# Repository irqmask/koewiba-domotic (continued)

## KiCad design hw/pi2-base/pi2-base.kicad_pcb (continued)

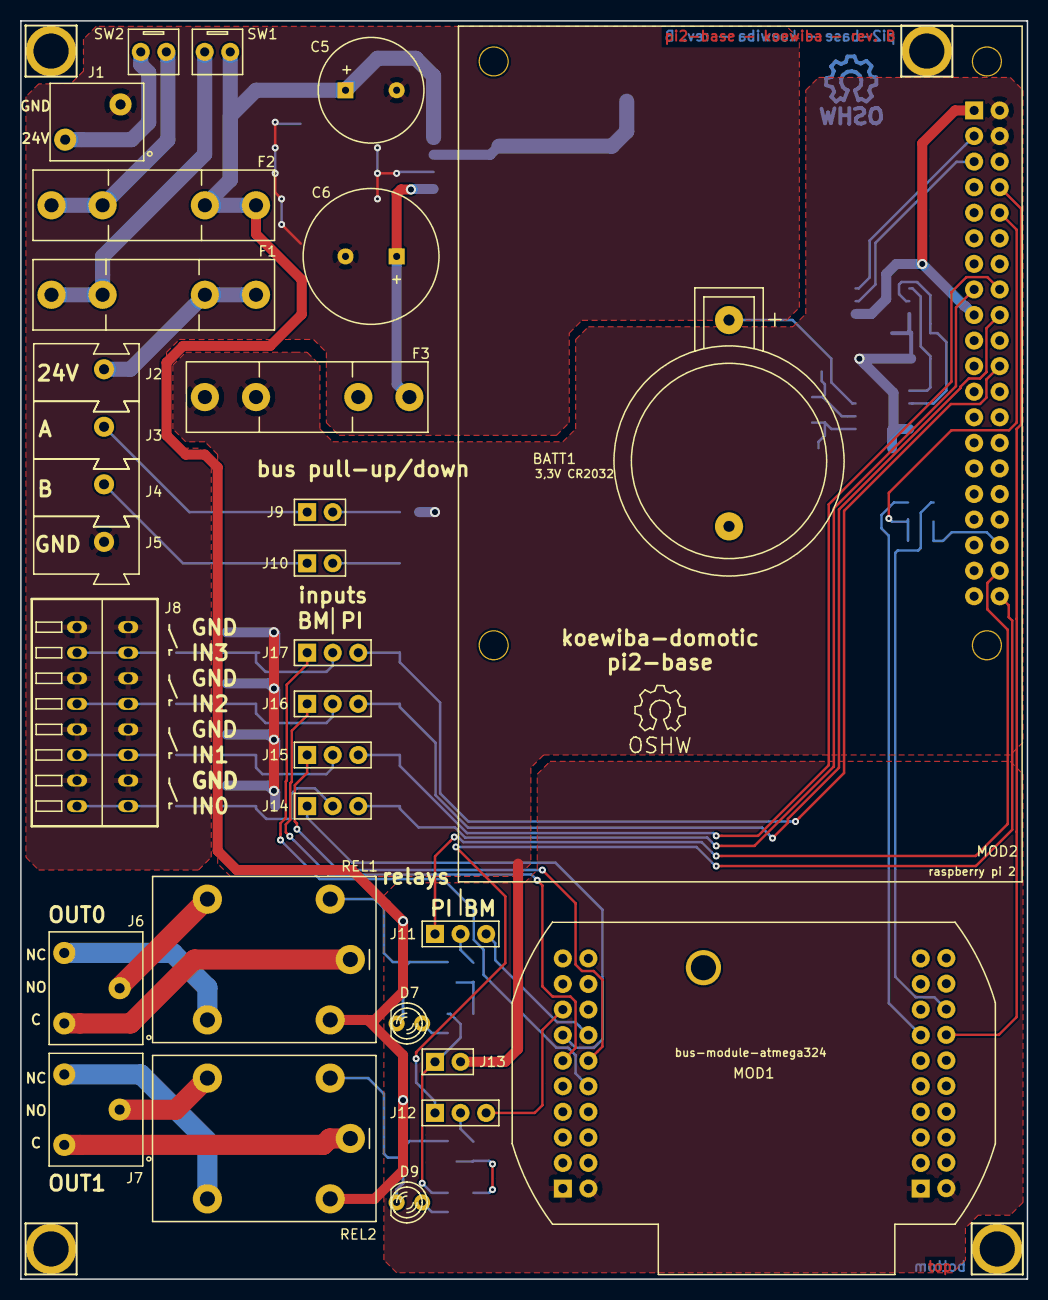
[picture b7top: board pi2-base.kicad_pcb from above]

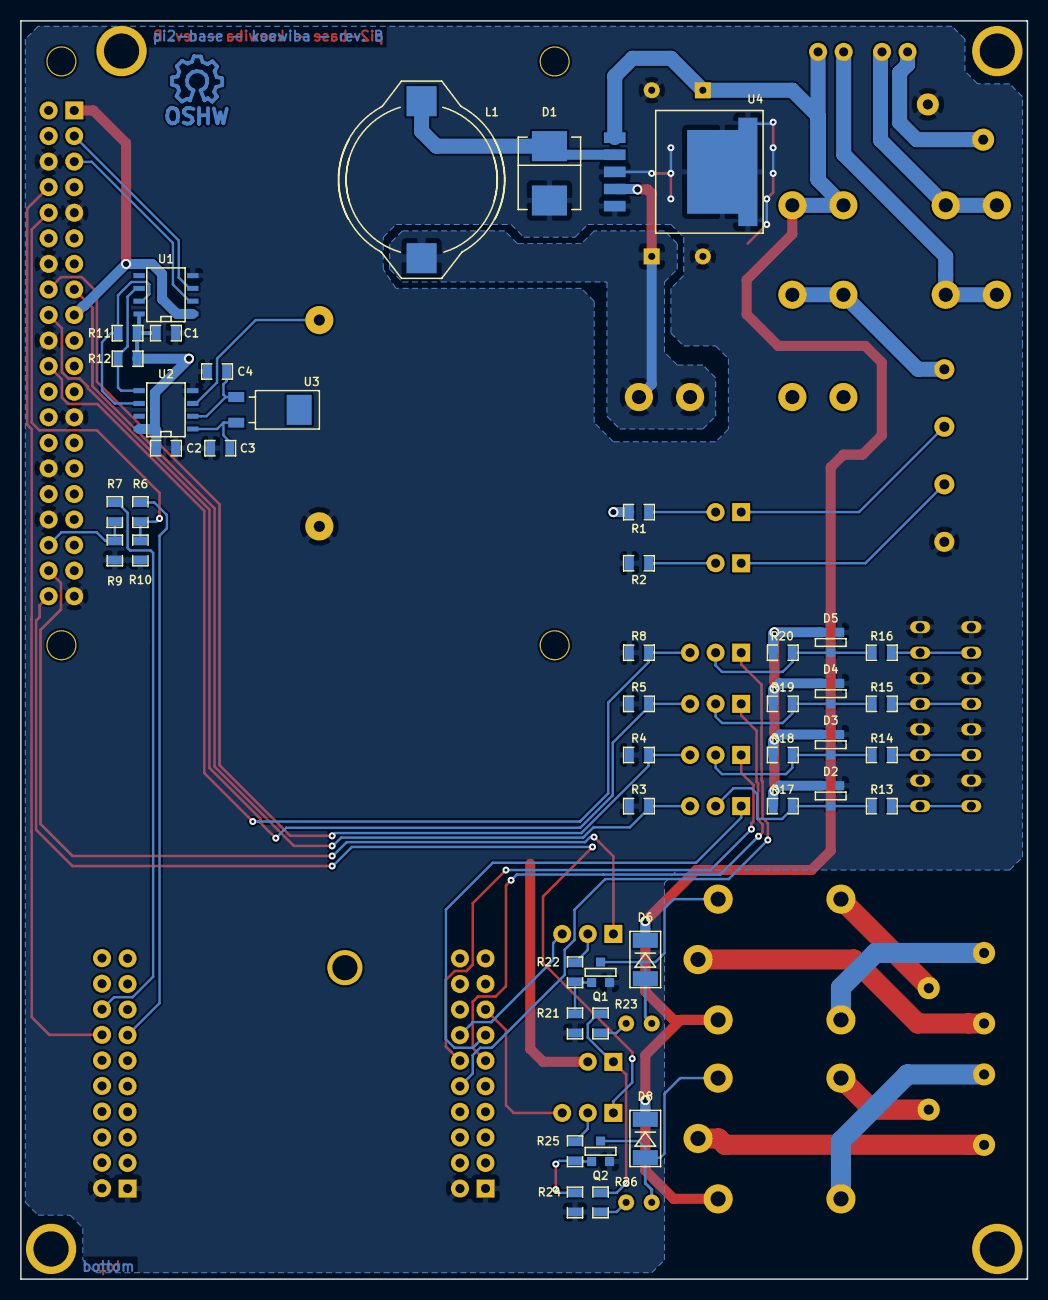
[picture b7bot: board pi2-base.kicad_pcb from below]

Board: 2 copper layers, 100.0 x 125.0 mm, 81 parts (45 on the bottom side), 61 nets.

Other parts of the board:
Symbol_OSHW-Logo_SilkScreen: Open Source Hardware; Symbol_OSHW-Logo_SilkScreen

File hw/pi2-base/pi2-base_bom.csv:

"Id";"Bezeichner";"Gehäuse";"Stückzahl";"Bezeichnung";"Anbieter und Ref";
1;"U4";"TO263_5";1;"LM2576";;;
2;"C6";"CP_RM5.08mm_D13.5mm";1;"1000uF";;;
3;"C5";"CP_RM5.08mm_D10.5mm";1;"100uF";;;
4;"J2";"WAGO243";1;"WAGO 243 orange";;;
5;"J3";"WAGO243";1;"WAGO 243 green";;;
6;"J4";"WAGO243";1;"WAGO 243 grey";;;
7;"J5";"WAGO243";1;"WAGO 243 blue";;;
8;"REL1,REL2";"omron_G5LE-1";2;"OMRON_G5LE-1";;;
9;"LOGO1";"Symbol_OSHW-Logo_Copper";1;"OPEN HARDWARE";;;
10;"Symbol_OSHW-Logo_SilkScreen";"Symbol_OSHW-Logo_SilkScreen";1;"Open Source Hardware";;;
11;"MOD2";"raspberry_pi2";1;"Raspberry_Pi_B2";;;
12;"BATT1";"CR2032H";1;"3V";;;
13;"MOD1";"bus-module_atmega324";1;"bus-module_atmega324_revB";;;
14;"C1,C2";"C_0805";2;"100nF";;;
15;"C3,C4";"C_0805";2;"12.5pF";;;
16;"D1";"D_SMC";1;"B 340 F";;;
17;"D2,D3,D4,D5";"SOT23-3";4;"BAT54S";;;
18;"D6,D8";"D_MINIMELF";2;"1N4148";;;
19;"D7,D9";"LED_RM2.54mm_D3mm";2;"LED 2,2V 25mA";;;
20;"F1";"FUSE5-20";1;"250V 1A T";;;
21;"F2,F3";"FUSE5-20";2;"250V/2,5A T";;;
22;"J9";"HEADER_2x1";1;"BUS Pull-Up";;;
23;"J10";"HEADER_2x1";1;"BUS Pull-down";;;
24;"J13";"HEADER_2x1";1;"Power LEDs";;;
25;"L1";"L_PISR";1;"100uH";;;
26;"Q1,Q2";"SOT23-3";2;"BSS138";;;
27;"R1,R2,R23,R26";"R_0805";4;"1k";;;
28;"R3,R4,R5,R8";"R_0805";4;"100k";;;
29;"R6,R7,R11,R12,R21,R24";"R_0805";6;"10k";;;
30;"R9,R10";"R_0805";2;"18k";;;
31;"R13,R14,R15,R16";"R_0805";4;"4k7";;;
32;"R17,R18,R19,R20";"R_0805";4;"56k";;;
33;"R22,R25";"R_0805";2;"100";;;
34;"SW1";"PCB_CON2";1;"SWITCH";;;
35;"SW2";"PCB_CON2";1;"MAIN";;;
36;"U1";"SO8E";1;"PCA9517";;;
37;"U2";"SO8E";1;"DS1307";;;
38;"U3";"CRY_MS1V-7_SMD";1;"32.768kHz";;;
39;"J11,J12,J14,J15,J16,J17";"HEADER_3x1";6;"JUMPER3";;;
40;"H1,H2,H3,H4";"HOLE_3.5mm";4;"HOLE";;;
41;"J7,J6";"WAGO_2081-1123";2;"WAGO 2081-1123";;;
42;"J1";"WAGO_2081-1122";1;"WAGO 2081-1122";;;
43;"J8";"WAGO_233-8";1;"WAGO 233-508";;;
